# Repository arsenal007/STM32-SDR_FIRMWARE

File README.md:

Low cost "sandwich" SDR TRX UT3MK Tranciever PCB layout and software
  - click on images to enlarge

 - Schematics

 - Gerber files

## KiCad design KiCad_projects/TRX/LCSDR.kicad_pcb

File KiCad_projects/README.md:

Low cost "sandwich" SDR TRX UT3MK Tranciever PCB layout

(click on images to enlarge)
VFO Mainboard 
 - Schematics

 - Gerber files, 3D models

VFO Front PCB with Keyboard, Encoder (EC16) and LCD
 - Schematics

 - Gerber files, 3D models

BPF

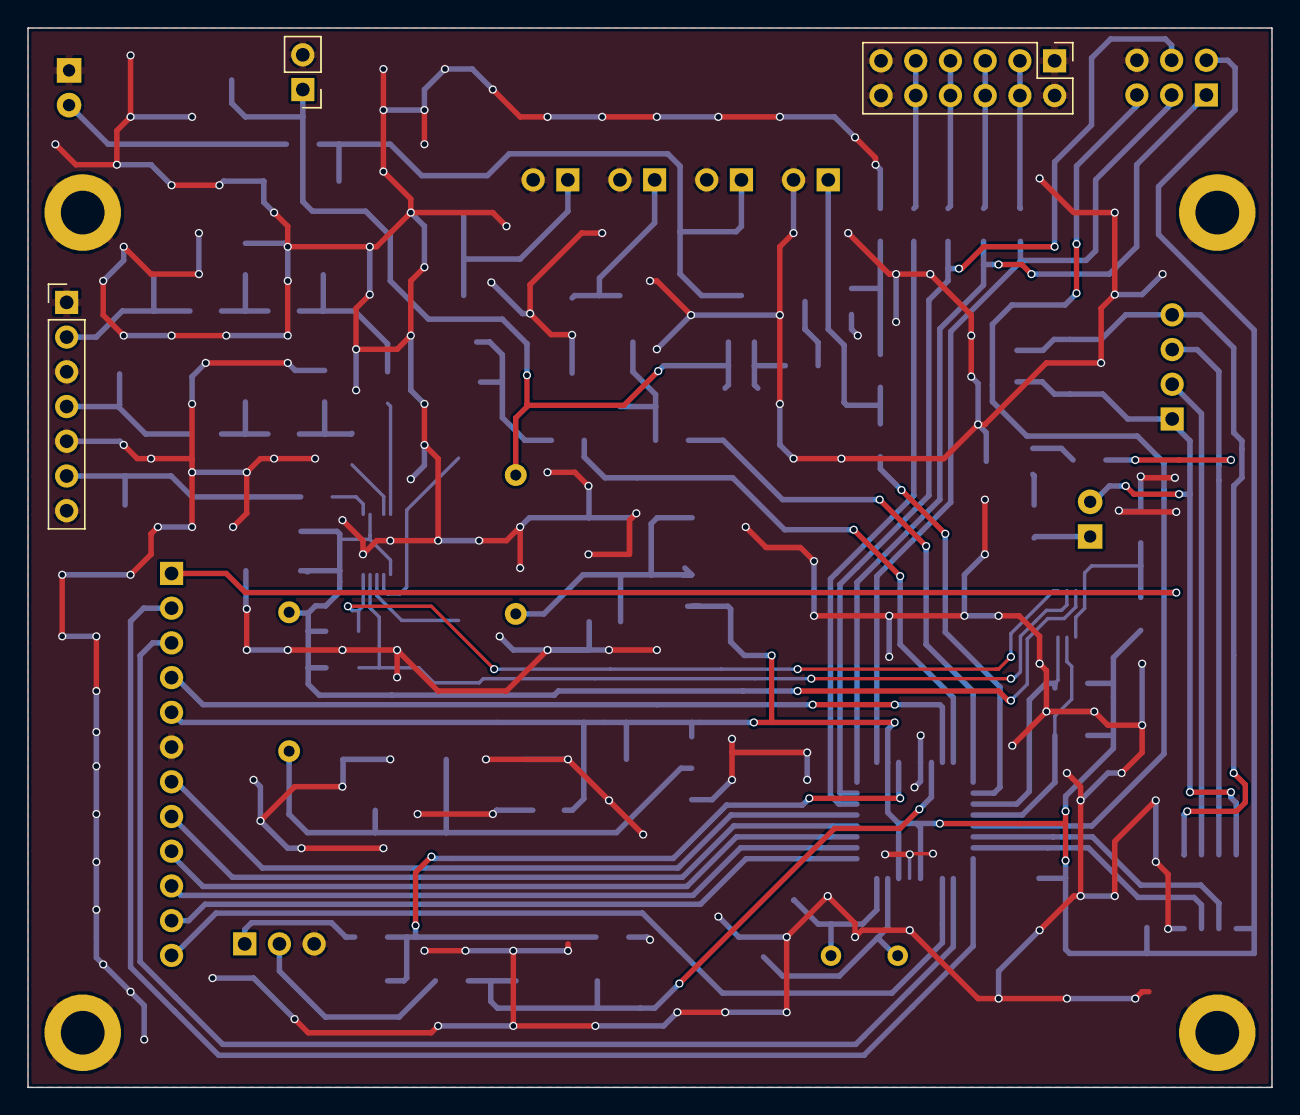
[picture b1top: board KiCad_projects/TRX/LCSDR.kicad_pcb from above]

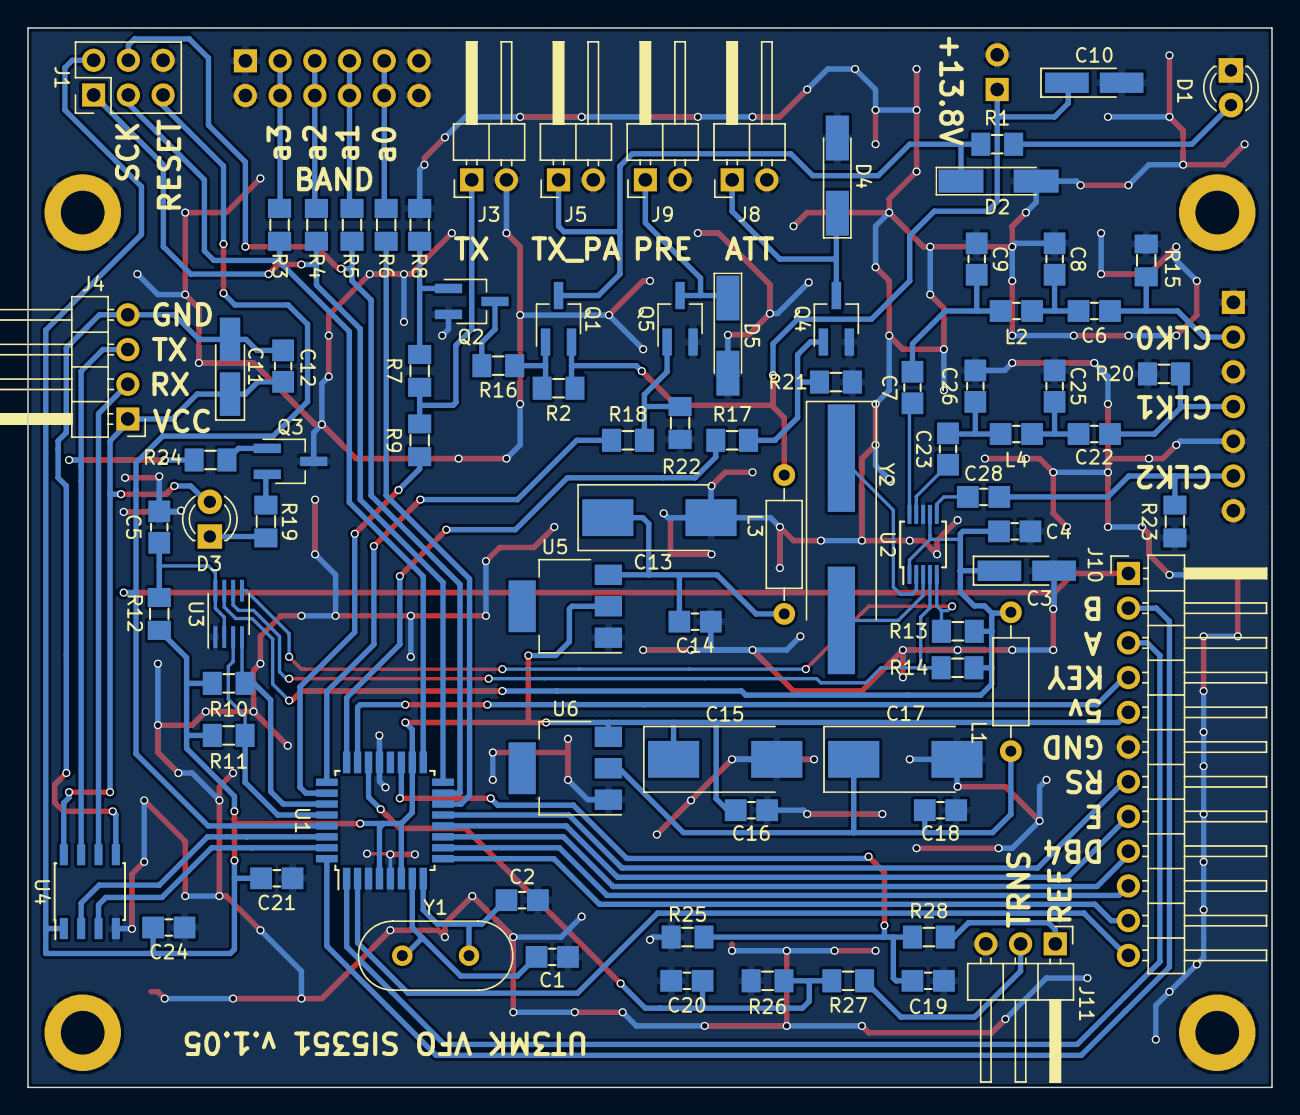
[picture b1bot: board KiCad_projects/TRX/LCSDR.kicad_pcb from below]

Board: 2 copper layers, 91.0 x 77.5 mm, 92 parts (85 on the bottom side), 69 nets.

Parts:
C1, C2, C8, C9, C25, C26: 22pF; C_1206_0603
C3, C10, C11: 10uF; CP_Tantalum_Case-A_EIA-3216-18_Hand
C4, C5, C6, C12, C14, C16, C18, C19, C20, C21, C22, C24: 100nF; C_1206_0603
C7, C23, C28: 10nF; C_1206_0603
C13, C15, C17: 100uF; CP_Tantalum_Case-D_EIA-7343-31_Hand
D1, D3: LED; LED_D3.0mm
D2, D4, D5: 4148; D_MiniMELF_Handsoldering
J1: SPI; Pin_Header_Straight_2x03_Pitch2.54mm
J2: BAND; Pin_Header_Straight_2x06_Pitch2.54mm
J3: OUT-TX; Pin_Header_Angled_1x02_Pitch2.54mm
J4: UART; Pin_Header_Angled_1x04_Pitch2.54mm
J5: PA; Pin_Header_Angled_1x02_Pitch2.54mm
J6: 12v; Pin_Header_Straight_1x02_Pitch2.54mm
J7: OUT; Pin_Header_Straight_1x07_Pitch2.54mm
J8: ATT; Pin_Header_Angled_1x02_Pitch2.54mm
J9: PRE; Pin_Header_Angled_1x02_Pitch2.54mm
J10: MANAGEMENT; Pin_Header_Angled_1x12_Pitch2.54mm
J11: Conn_01x03; Pin_Header_Angled_1x03_Pitch2.54mm
J12, J13, J14, J15: Conn_01x01; MountingHole_3.2mm_M3_DIN965_Pad
L1, L3: 100uH; R_Axial_DIN0207_L6.3mm_D2.5mm_P10.16mm_Horizontal
L2, L4: 56nH; C_1206_0603
Q1, Q3: MMBT2907; SOT-23W_Handsoldering
Q2, Q4, Q5: MMBT2222; SOT-23W_Handsoldering
R1, R7, R16, R17, R18: 1k; R_1206_0603
R2, R8, R21, R22: 22k; R_1206_0603
R3, R4, R5, R6: 100R; R_1206_0603
R9: 30R; R_1206_0603
R10, R11: 4.7k; R_1206_0603
R12: 200k; R_1206_0603
R13, R14, R24, R25, R26, R27, R28: 2.2k; R_1206_0603
R15, R20, R23: 51R; R_1206_0603
R19: 510R; R_1206_0603
U1: ATMEGA328P-AU; TQFP-32_7x7mm_Pitch0.8mm
U2: Si5351; MSOP-10_3x3mm_Pitch0.5mm
U3: PCA9306; SSOP-8_2.95x2.8mm_Pitch0.65mm
U4: ADuM1201BR; SOIC-8_3.9x4.9mm_Pitch1.27mm
U5: LD1117S50TR; SOT-223
U6: LD1117S33TR; SOT-223
Y1: 16Mhz; Crystal_HC49-U_Vertical
Y2: 25Mhz; Crystal_SMD_HC49-SD_HandSoldering

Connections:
+3V3: C17.1, C18.1, L1.1, U6.2
+5V: C15.1, C16.1, C21.1, C24.1, J1.2, J10.5, R10.2, R11.2, R12.1, U1.4, U1.6, U1.18, U4.1, U5.2, U6.3
+12V: C10.1, J6.1, L3.1, Q1.2, R2.2
/A0: J2.9, J2.10, R6.2
/A1: J2.7, J2.8, R5.1
/A2: J2.5, J2.6, R4.1
/A3: J2.3, J2.4, R3.1
/ATT: R17.1, U1.24
/DB4: J10.9, U1.11
/DB5: J10.10, U1.10
/DB6: J10.11, U1.9
/DB7: J10.12, U1.2
/E: J10.8, U1.12
/ENCODER_A: J10.3, U1.1
/ENCODER_B: J10.2, U1.32
/KEYBOARD: J10.4, U1.23
/MISO: J1.1, R4.2, U1.16
/MOSI: J1.4, R5.2, U1.15
/PREAMP: R18.1, U1.25
/RESET: J1.5, J10.1, U1.29
/RS: J10.7, U1.13
/RX: J4.2, U4.6
/SCK: J1.3, R3.2, U1.17
/SCL4: R14.2, U2.4, U3.6
/SCL5: R11.1, U1.28, U3.3
/SDA4: R13.2, U2.5, U3.5
/SDA5: R10.1, U1.27, U3.4
/TX: J4.3, R24.2, U4.7
GND: C1.2, C2.2, C3.2, C4.2, C5.2, C8.2, C9.2, C10.2, C13.2, C14.2, C15.2, C16.2, C17.2, C18.2, C19.1, C20.1, C21.2, C24.2, C25.2, C26.2, D1.1, D2.2, D4.2, D5.2, J1.6, J2.1, J2.2, J2.11, J2.12, J3.2, J5.2, J6.2, J7.1, J7.3, J7.5, J7.7, J8.2, J9.2, J10.6, J11.3, J12.1, J13.1, J14.1, J15.1, Q2.2, Q3.3, Q4.2, Q5.2, R8.2, R15.2, R20.2, R21.2, R22.1, R23.2, R25.2, R26.2, U1.3, U1.5, U1.21, U2.8, U3.1, U4.4, U5.1, U6.1
unnamed: C1.1, U1.7, Y1.1
unnamed: C2.1, U1.8, Y1.2
unnamed: C3.1, C4.1, L1.2, R13.1, R14.1, U2.1, U2.7, U3.7
unnamed: C5.1, R12.2, U3.2, U3.8
unnamed: C6.1, J7.2, R15.1
unnamed: C6.2, C8.1, L2.1
unnamed: C7.1, C9.1, L2.2
unnamed: C7.2, U2.10
unnamed: C11.1, C12.1, D3.2, J4.1, U4.8
unnamed: C11.2, C12.2, J4.4, U4.5
unnamed: C13.1, C14.1, L3.2, U5.3
unnamed: C19.2, R25.1, R28.1, U1.19
unnamed: C20.2, R26.1, R27.1, U1.22
unnamed: C22.1, J7.4, R20.1
unnamed: C22.2, C25.1, L4.1
unnamed: C23.1, C26.1, L4.2
unnamed: C23.2, U2.9
unnamed: C28.1, J7.6, R23.1
unnamed: C28.2, U2.6
unnamed: D1.2, R1.2
unnamed: D2.1, J5.1, Q1.3, R1.1
unnamed: D3.1, R19.1
unnamed: D4.1, J8.1, Q4.3
unnamed: D5.1, J9.1, Q5.3
unnamed: J3.1, R7.1, R9.2
unnamed: J11.1, R28.2
unnamed: J11.2, R27.2
unnamed: Q1.1, R2.1, R16.2
unnamed: Q2.1, R7.2, R8.1
unnamed: Q2.3, R16.1
unnamed: Q3.1, R24.1
unnamed: Q3.2, R19.2
unnamed: Q4.1, R17.2, R21.1
unnamed: Q5.1, R18.2, R22.2
unnamed: R6.1, U1.14
unnamed: R9.1, U1.26
unnamed: U1.30, U4.2
unnamed: U1.31, U4.3
unnamed: U2.2, Y2.1
unnamed: U2.3, Y2.2

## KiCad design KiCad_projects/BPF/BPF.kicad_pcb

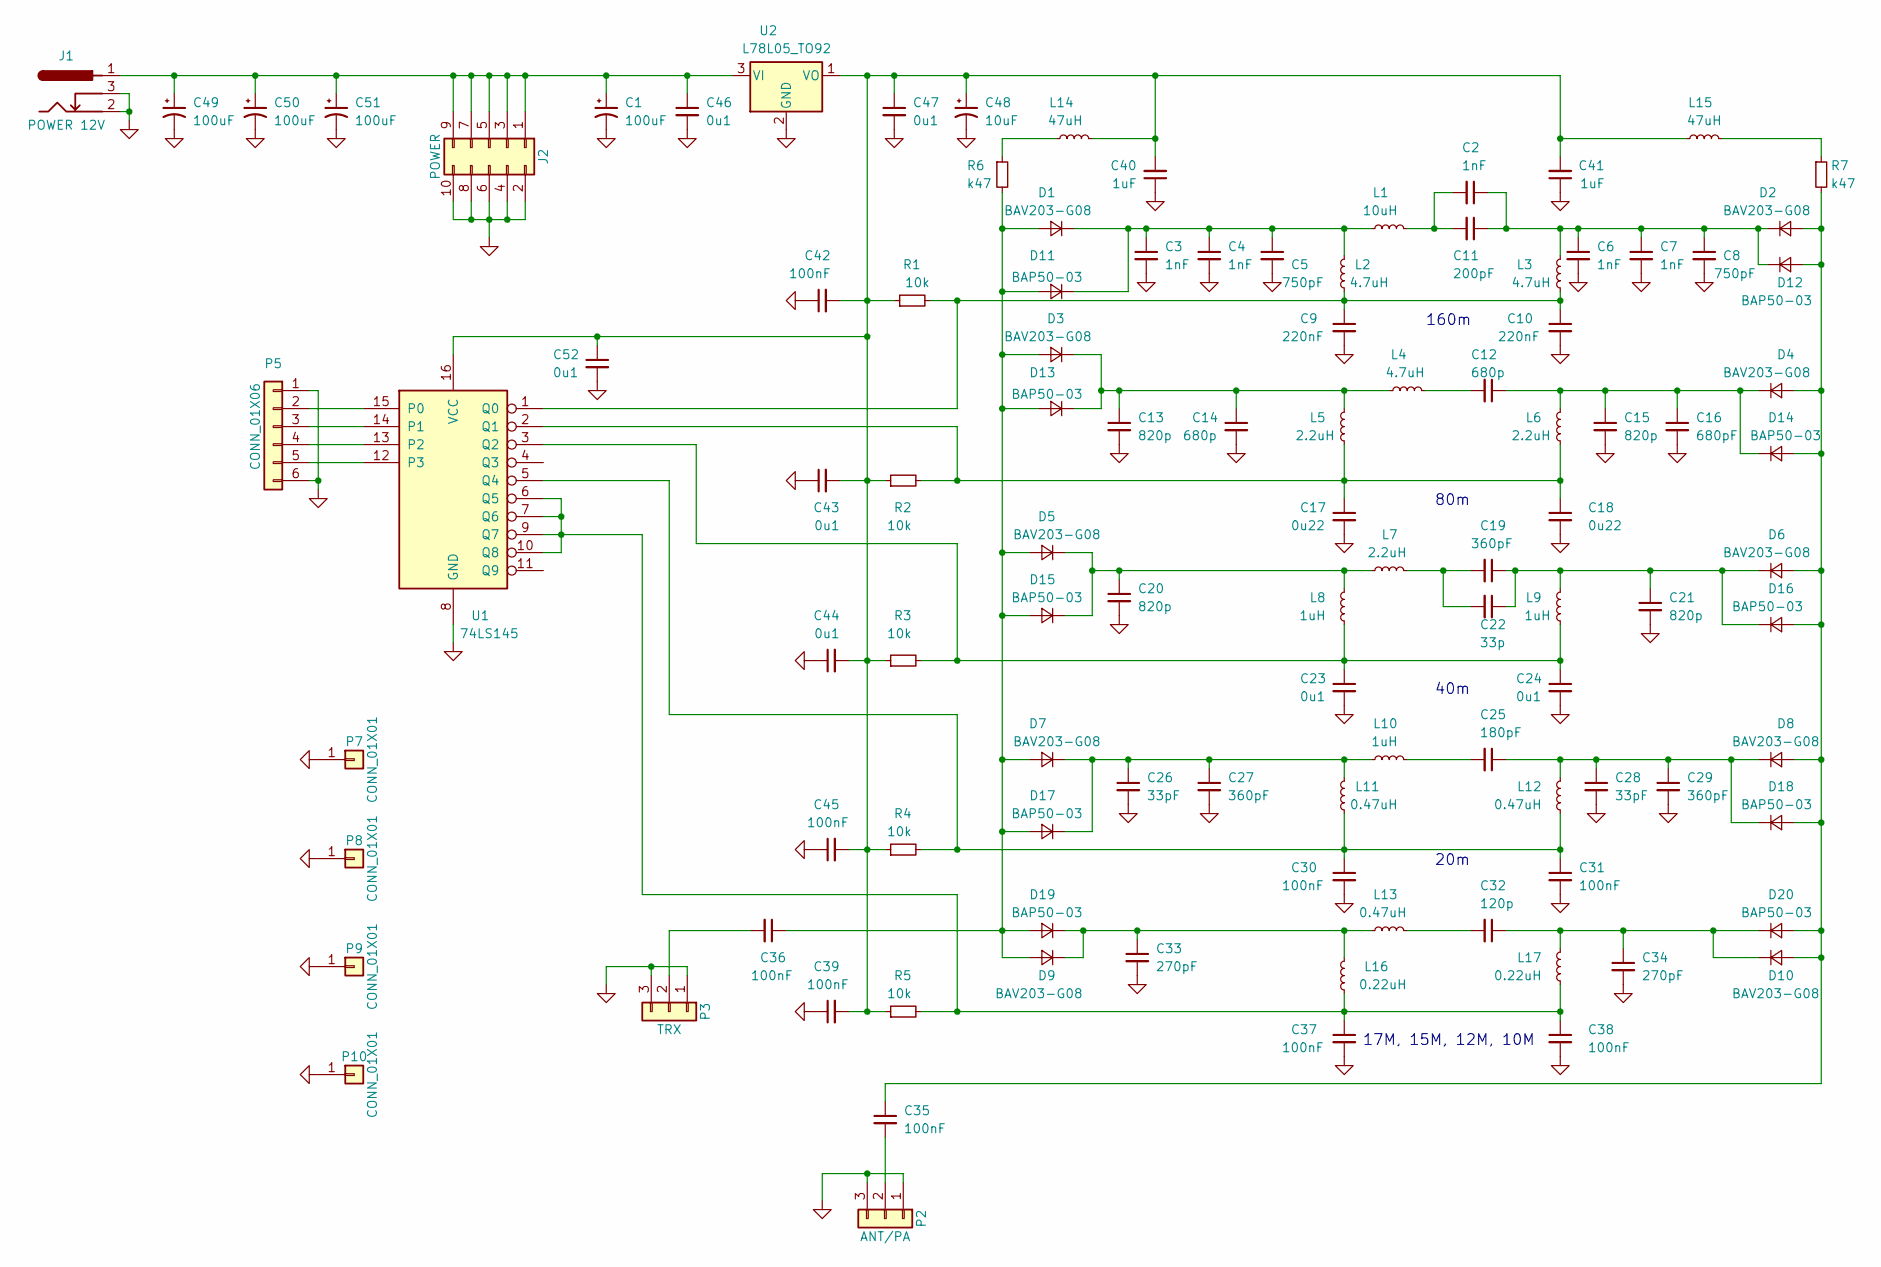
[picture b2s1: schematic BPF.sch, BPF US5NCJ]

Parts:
C1, C49, C50, C51: 100uF; CP_Radial_D6.3mm_P2.50mm
C2, C3, C4, C6, C7: 1nF; C_1206_0603
C5, C8: 750pF; C_0603_HandSoldering
C9, C10: 220nF; C_0603_HandSoldering
C11: 200pF; C_0603_HandSoldering
C12, C14: 680p; C_0603_HandSoldering
C13, C15, C20, C21: 820p; C_0603_HandSoldering
C16: 680pF; C_0603_HandSoldering
C17, C18: 0u22; C_0603_HandSoldering
C19, C27, C29: 360pF; C_0603_HandSoldering
C22: 33p; C_1206_0603
C23, C24, C43, C44, C46, C47, C52: 0u1; C_1206_0603
C25: 180pF; C_1206_0603
C26, C28: 33pF; C_1206_0603
C30, C31, C35, C36, C37, C38, C39, C42, C45: 100nF; C_1206_0603
C32: 120p; C_0603_HandSoldering
C33, C34: 270pF; C_1206_0603
C40, C41: 1uF; C_1206_0603
C48: 10uF; Universal_C_Radial_D5_L11_P2_tantal
D1, D2, D3, D4, D5, D6, D7, D8, D9, D10: BAV203-G08; MiniMELF_Standard
D11, D12, D13, D14, D15, D16, D17, D18, D19, D20: BAP50-03; SOD-323_HandSoldering
J1: POWER 12V; BARREL_JACK
J2: POWER; Pin_Header_Straight_2x05_Pitch2.54mm
L1: 10uH; Resistor_SMD+THTuniversal_0603to2512_RM10_HandSoldering
L2, L3, L4: 4.7uH; Resistor_SMD+THTuniversal_0603to2512_RM10_HandSoldering
L5, L6, L7: 2.2uH; Resistor_SMD+THTuniversal_0603to2512_RM10_HandSoldering
L8, L9, L10: 1uH; Resistor_SMD+THTuniversal_0603to2512_RM10_HandSoldering
L11, L12, L13: 0.47uH; Resistor_SMD+THTuniversal_0603to2512_RM10_HandSoldering
L14, L15: 47uH; Resistor_Horizontal_RM10mm
L16, L17: 0.22uH; Resistor_SMD+THTuniversal_0603to2512_RM10_HandSoldering
P2: ANT/PA; Pin_Header_Straight_1x03
P3: TRX; Pin_Header_Straight_1x03
P5: CONN_01X06; Pin_Header_Straight_1x06_Pitch2.54mm
P7, P8, P9, P10: CONN_01X01; MountingHole_3.2mm_M3_ISO14580_Pad
R1, R2, R3, R4, R5: 10k; R_1206_0603
R6, R7: k47; R_1206_0603
U1: 74LS145; SOIC-16_3.9x9.9mm_Pitch1.27mm
U2: L78L05_TO92; TO-92_Inline_Wide

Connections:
GND: C1.2, C3.2, C4.2, C5.2, C6.2, C7.2, C8.2, C9.2, C10.2, C13.2, C14.2, C15.2, C16.2, C17.2, C18.2, C20.2, C21.2, C23.2, C24.2, C26.2, C27.2, C28.2, C29.2, C30.2, C31.2, C33.2, C34.2, C37.2, C38.2, C39.1, C40.1, C41.1, C42.1, C43.1, C44.1, C45.1, C46.2, C47.2, C48.2, C49.2, C50.2, C51.2, C52.2, J1.2, J1.3, J2.2, J2.4, J2.6, J2.8, J2.10, P2.1, P2.3, P3.1, P3.3, P5.1, P5.6, P7.1, P8.1, P9.1, P10.1, U1.8 (GND), U2.2 (GND)
unnamed: C1.1, C46.1, C49.1, C50.1, C51.1, J1.1, J2.1, J2.3, J2.5, J2.7, J2.9, U2.3 (VI)
unnamed: C3.1, C4.1, C5.1, D1.1 (K), D11.1 (K), L1.1, L2.2
unnamed: C9.1, C10.1, L2.1, L3.1, R1.2, U1.1 (Q0)
unnamed: C2.1, C6.1, C7.1, C8.1, C11.1, D2.1 (K), D12.1 (K), L3.2
unnamed: C2.2, C11.2, L1.2
unnamed: C12.1, C15.1, C16.1, D4.1 (K), D14.1 (K), L6.2
unnamed: C12.2, L4.2
unnamed: C13.1, C14.1, D3.1 (K), D13.1 (K), L4.1, L5.2
unnamed: C17.1, C18.1, L5.1, L6.1, R2.2, U1.2 (Q1)
unnamed: C19.1, C21.1, C22.1, D6.1 (K), D16.1 (K), L9.2
unnamed: C19.2, C22.2, L7.2
unnamed: C20.1, D5.1 (K), D15.1 (K), L7.1, L8.2
unnamed: C23.1, C24.1, L8.1, L9.1, R3.2, U1.3 (Q2)
unnamed: C25.1, C28.1, C29.1, D8.1 (K), D18.1 (K), L12.2
unnamed: C25.2, L10.2
unnamed: C26.1, C27.1, D7.1 (K), D17.1 (K), L10.1, L11.2
unnamed: C30.1, C31.1, L11.1, L12.1, R4.2, U1.5 (Q4)
unnamed: C32.1, C34.1, D10.1 (K), D20.1 (K), L17.2
unnamed: C32.2, L13.2
unnamed: C33.1, D9.1 (K), D19.1 (K), L13.1, L16.2
unnamed: C35.1, D2.2 (A), D4.2 (A), D6.2 (A), D8.2 (A), D10.2 (A), D12.2 (A), D14.2 (A), D16.2 (A), D18.2 (A), D20.2 (A), R7.2
unnamed: C35.2, P2.2
unnamed: C36.1, D1.2 (A), D3.2 (A), D5.2 (A), D7.2 (A), D9.2 (A), D11.2 (A), D13.2 (A), D15.2 (A), D17.2 (A), D19.2 (A), R6.2
unnamed: C36.2, P3.2
unnamed: C37.1, C38.1, L16.1, L17.1, R5.2, U1.6 (Q5), U1.7 (Q6), U1.9 (Q7), U1.10 (Q8)
unnamed: C39.2, C40.2, C41.2, C42.2, C43.2, C44.2, C45.2, C47.1, C48.1, C52.1, L14.2, L15.1, R1.1, R2.1, R3.1, R4.1, R5.1, U1.16 (VCC), U2.1 (VO)
unnamed: L14.1, R6.1
unnamed: L15.2, R7.1
unnamed: P5.2, U1.15 (P0)
unnamed: P5.3, U1.14 (P1)
unnamed: P5.4, U1.13 (P2)
unnamed: P5.5, U1.12 (P3)

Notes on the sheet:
160m
80m
40m
20m
17M, 15M, 12M, 10M

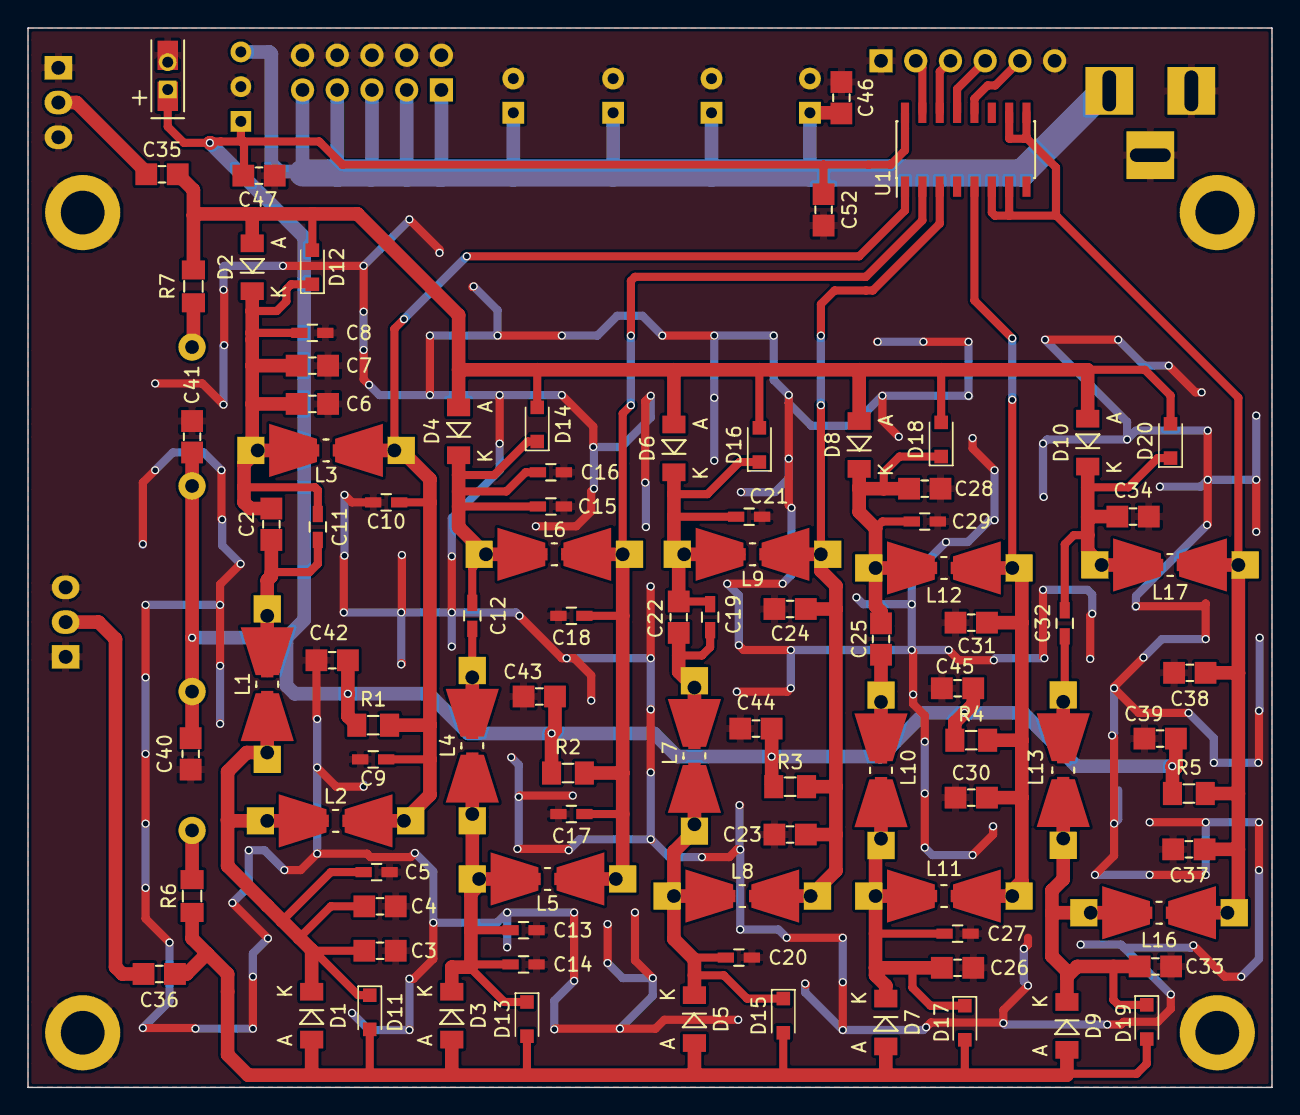
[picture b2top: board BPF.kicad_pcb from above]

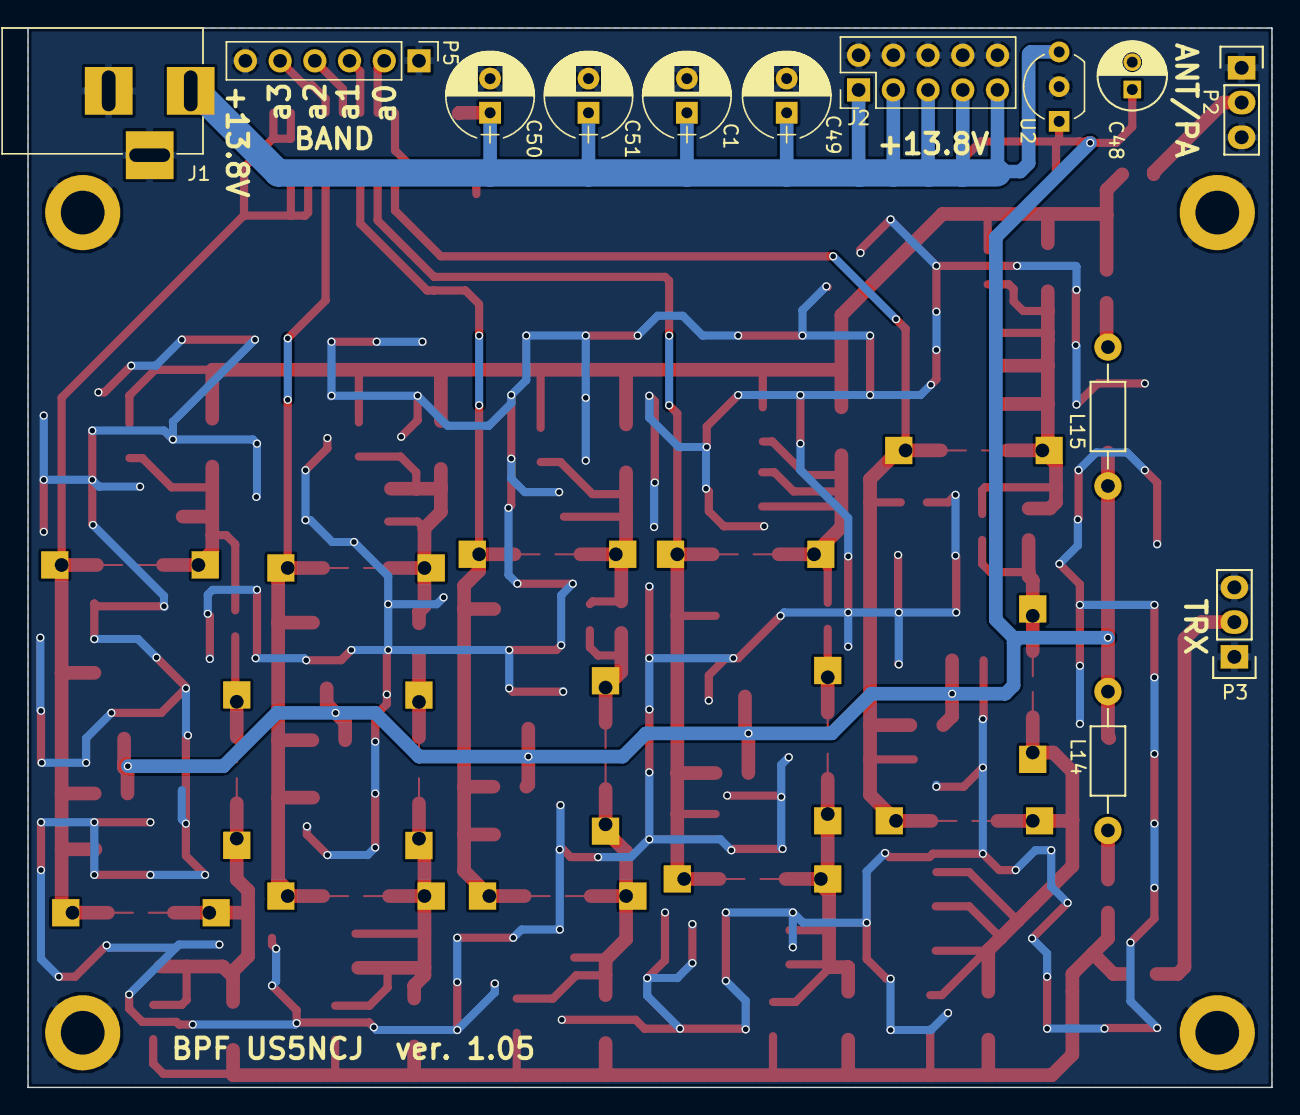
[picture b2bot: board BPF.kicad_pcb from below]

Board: 2 copper layers, 91.0 x 77.5 mm, 107 parts (14 on the bottom side), 33 nets.

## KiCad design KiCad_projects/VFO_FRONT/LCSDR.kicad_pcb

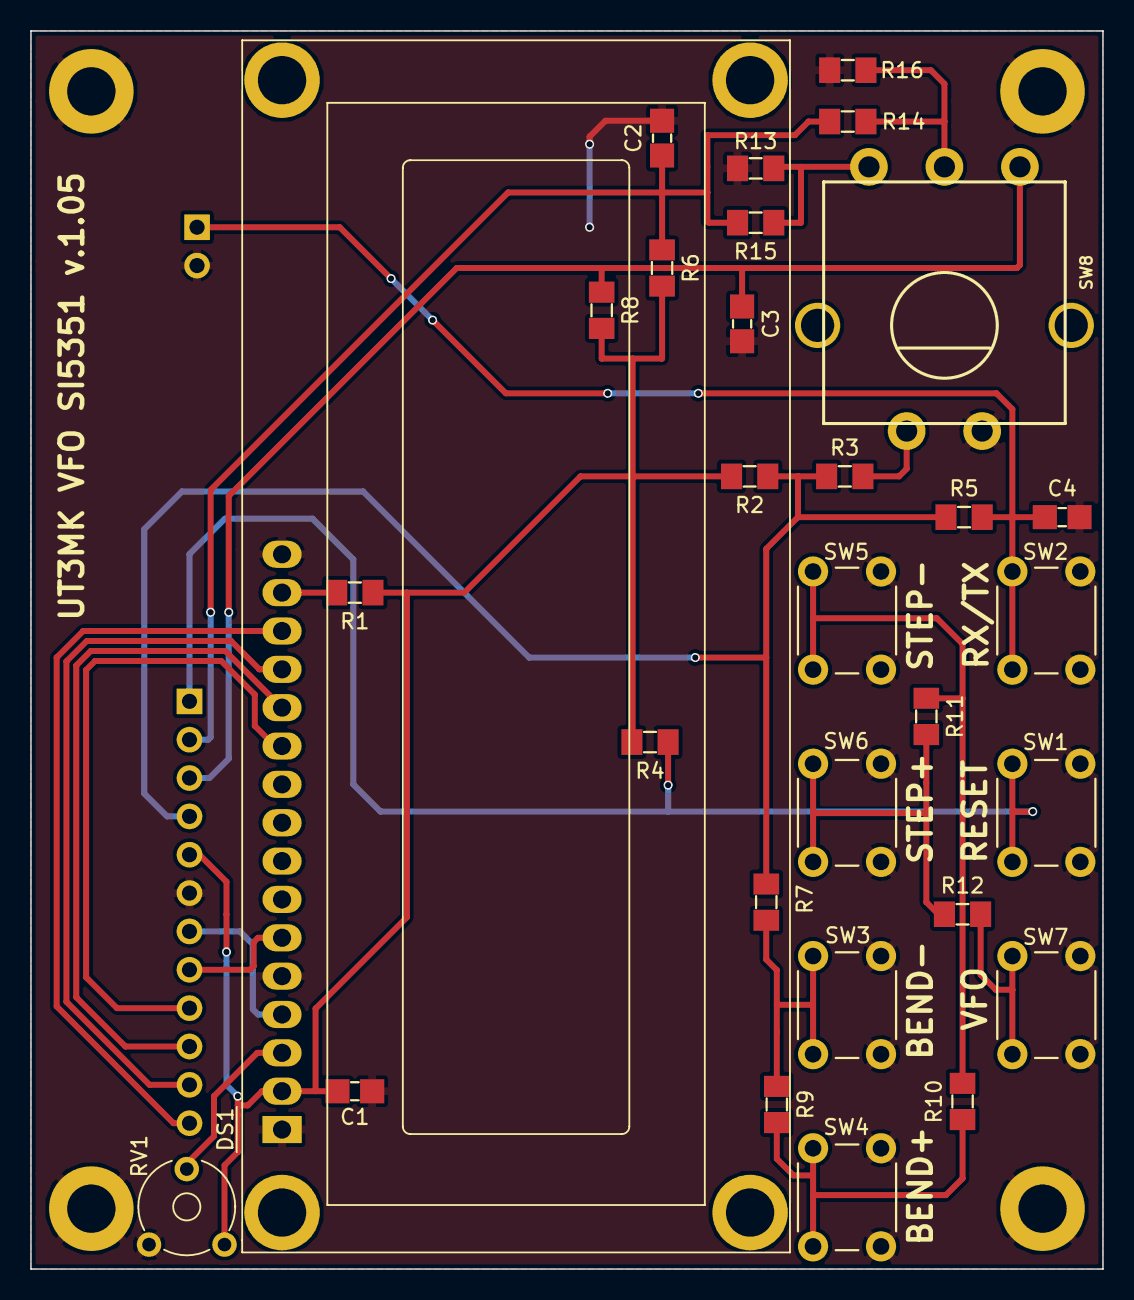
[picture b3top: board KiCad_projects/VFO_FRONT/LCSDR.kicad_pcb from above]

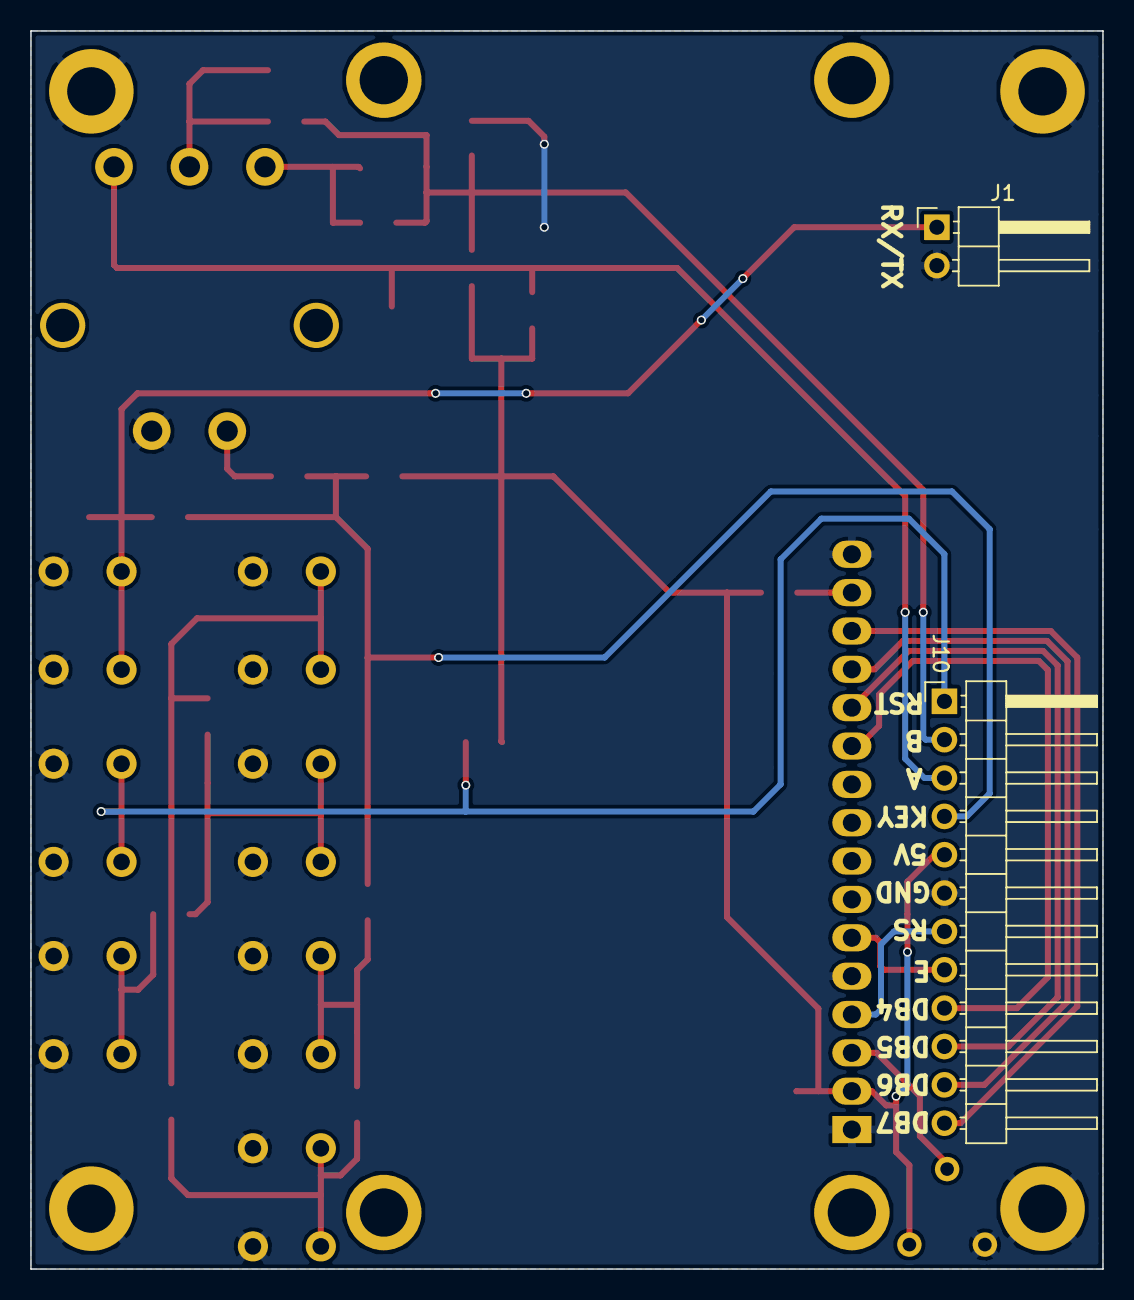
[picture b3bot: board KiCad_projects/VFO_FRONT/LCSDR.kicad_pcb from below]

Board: 2 copper layers, 71.0 x 82.0 mm, 36 parts (2 on the bottom side), 23 nets.

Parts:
C1, C2, C3, C4: 100nF; C_1206_0603
DS1: WC1602A
J1: RX/TX; Pin_Header_Angled_1x02_Pitch2.54mm
J10: MANAGEMENT; Pin_Header_Angled_1x12_Pitch2.54mm
J12, J13, J14, J15: Conn_01x01; MountingHole_3.2mm_M3_DIN965_Pad
R1: 10R; R_1206_0603
R2, R3: 15k; R_1206_0603
R4, R6, R8: 10k; R_1206_0603
R5: 150; R_1206_0603
R7, R9, R10, R11: 1k; R_1206_0603
R12: 3.3k; R_1206_0603
R13, R14, R15, R16: 0; R_1206_0603
RV1: 22k; Potentiometer_Trimmer_Piher_PT-6v_Horizontal
SW1: RESET; SW_PUSH_6mm_h13mm
SW2: RX/TX; SW_PUSH_6mm_h13mm
SW3: BEND-; SW_PUSH_6mm_h13mm
SW4: BEND+; SW_PUSH_6mm_h13mm
SW5: STEP-; SW_PUSH_6mm_h13mm
SW6: STEP+; SW_PUSH_6mm_h13mm
SW7: OSCEL; SW_PUSH_6mm_h13mm
SW8: Rotary_Encoder_Switch; SF-ROTARY-ENCODER

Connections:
+5V: C1.1, DS1.2, J10.5, R1.1, R2.2, R4.2, R6.2, R8.2, RV1.1
/DB4: DS1.11, J10.9
/DB5: DS1.12, J10.10
/DB6: DS1.13, J10.11
/DB7: DS1.14, J10.12
/E: DS1.6, J10.8
/ENCODER_A: C3.1, J10.3, R8.1, SW8.1
/ENCODER_B: C2.1, J10.2, R6.1, R13.1, R14.2
/KEYBOARD: J10.4, R2.1, R3.1, R5.1, R7.1
/RESET: J10.1, R4.1, SW1.1
/RS: DS1.4, J10.7
GND: C1.2, C2.2, C3.2, C4.2, DS1.1, DS1.5, DS1.16, J1.2, J10.6, J12.1, J13.1, J14.1, J15.1, R15.2, R16.2, RV1.3, SW1.2, SW2.2, SW3.2, SW4.2, SW5.2, SW6.2, SW7.2, SW8.4
unnamed: C4.1, J1.1, R5.2, SW2.1
unnamed: DS1.3, RV1.2
unnamed: DS1.15, R1.2
unnamed: R3.2, SW8.5
unnamed: R7.2, R9.1, SW3.1
unnamed: R9.2, R10.1, SW4.1
unnamed: R10.2, R11.1, SW5.1
unnamed: R11.2, R12.1, SW6.1
unnamed: R12.2, SW7.1
unnamed: R13.2, R15.1, SW8.3
unnamed: R14.1, R16.1, SW8.2

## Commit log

2017-12-27 first commit only VFO pcb KiCad
2017-12-27 adding pictures and correcting readme
2017-12-27 correcting readme
2017-12-28 modified VFO schematics and PCB. clk0/clk1/clk2, unified management board
2017-12-29 Separate boards for VFO, CLK0, CLK1, CLK2 and SWR
2018-01-01 Add BPF PCB and Schematics
2018-01-01 Fix some small issues and first tantal release
2018-01-01 Fix Issues with PCB Silk Text
2018-01-01 Update GRB-files of VFO_FRONT PCB
2018-01-09 add TRX
